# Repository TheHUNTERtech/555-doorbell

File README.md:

# 555-doorbell

A simple doorbell with two tones with the famous 555 timer.

It's an interesting circuit to learn the basics of the [555](https://en.wikipedia.org/wiki/555_timer_IC) and to learn how to solder and fabricate DIY a Through-Hole printed circuit board.

Also it's useful to learn the basics of EDA free-software [KiCad](http://kicad-pcb.org/).

This design was created to the [MakersUPV](https://makersupv.com) Workshop: [Taller fabricación casera de circuitos impresos](https://github.com/makers-upv/taller-pcb) (in Spanish)

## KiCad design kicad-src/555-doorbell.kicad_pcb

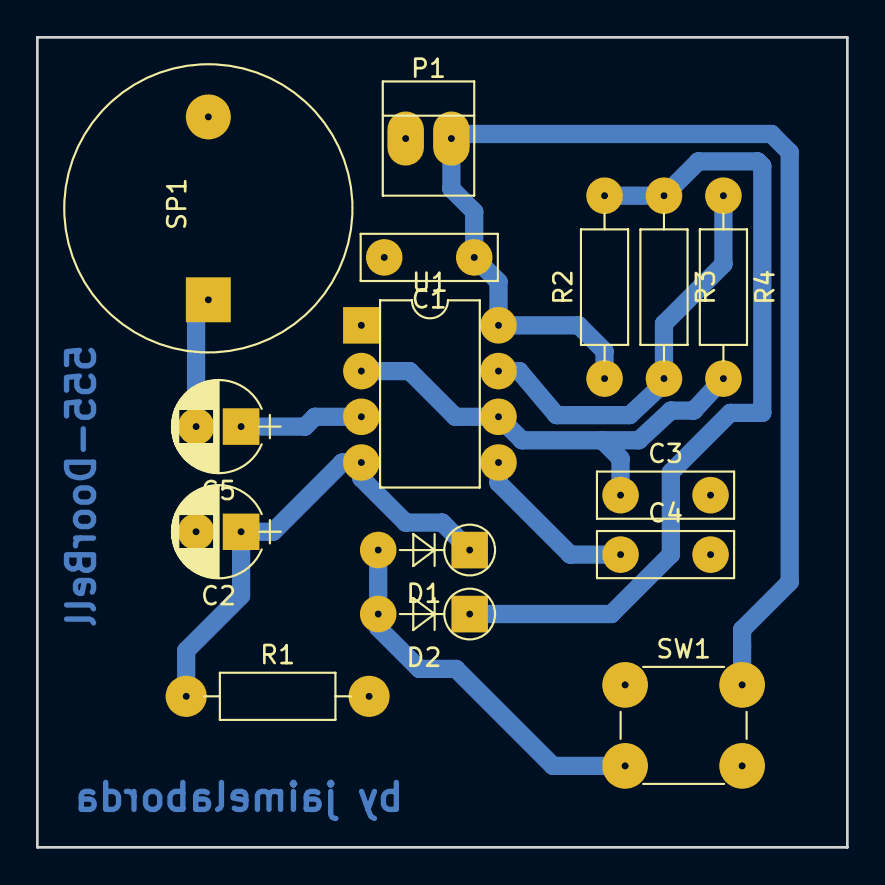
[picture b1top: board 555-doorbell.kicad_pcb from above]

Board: 2 copper layers, 45.0 x 45.0 mm, 15 parts (0 on the bottom side), 10 nets.

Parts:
C1, C3, C4: 10n; C_Disc_D7.5mm_W2.5mm_P5.00mm
C2, C5: 10u; CP_Radial_D5.0mm_P2.50mm
D1, D2: 1N4148; D_A-405_P5.08mm_Vertical_AnodeUp
P1: CONN_01X02; PINHEAD1-2
R1, R2, R3, R4: 47k; R_Axial_DIN0207_L6.3mm_D2.5mm_P10.16mm_Horizontal
SP1: SPEAKER; BUZZER
SW1: SW_PUSH_SMALL_H; SW_PUSH_6mm
U1: LM555N; DIP-8_W7.62mm

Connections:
GND: C1.2, C2.2, C3.2, C4.2, P1.1, R1.2, SP1.2, U1.1
unnamed: C2.1, D1.1, R1.1, U1.4
unnamed: C3.1, R4.2, U1.2, U1.6
unnamed: C4.1, U1.5
unnamed: C5.1, U1.3
unnamed: C5.2, SP1.1
unnamed: D1.2, D2.2, SW1.2
unnamed: D2.1, R2.2, R3.1
unnamed: R3.2, R4.1, U1.7
VCC: C1.1, P1.2, R2.1, SW1.1, U1.8

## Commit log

2017-05-27 :boom::camel: Added .gitattributes & .gitignore files
2017-05-27 Schematic v1 and pcb
    Design in progress
2017-05-28 pcb v1 finished
2017-05-30 Changes in the diammeter of the pads, re-do pdf
2017-06-03 Added BOM & FSilkS
2017-06-04 Added 3D render
